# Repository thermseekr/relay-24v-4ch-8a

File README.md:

# RELAY-24V-4CH-8A

Relay board with 4x 24 VDC relays rated for 8A. This board is designed to be used togheter with [ESP-24V-16CH](https://github.com/thermseekr/esp-24v-16ch) and [ESP-24V-32CH](https://github.com/thermseekr/esp-24v-32ch), but can be driven by any 24V control circuit compatible with NPN inputs.

The dimensions are such that the boards can be mounted on a PCB DIN rail holder from the Brazilian manufacturer Metaltex, check [here](https://www.metaltex.com.br/produtos/componentes/suportes/sp7-suporte-para-montagem-de-placa-de-circuito-impresso-em-trilho-din) for details.

Board uses Omron 10A relays and is limited to 8A/channel per copper trace capacity.

## LICENSE

This project is licensed under the [Creative Commons BY-NC 4.0 License](https://creativecommons.org/licenses/by-nc/4.0/).
Commercial use is not permitted without prior written consent. See the [LICENSE.txt](LICENSE.txt) file for details.

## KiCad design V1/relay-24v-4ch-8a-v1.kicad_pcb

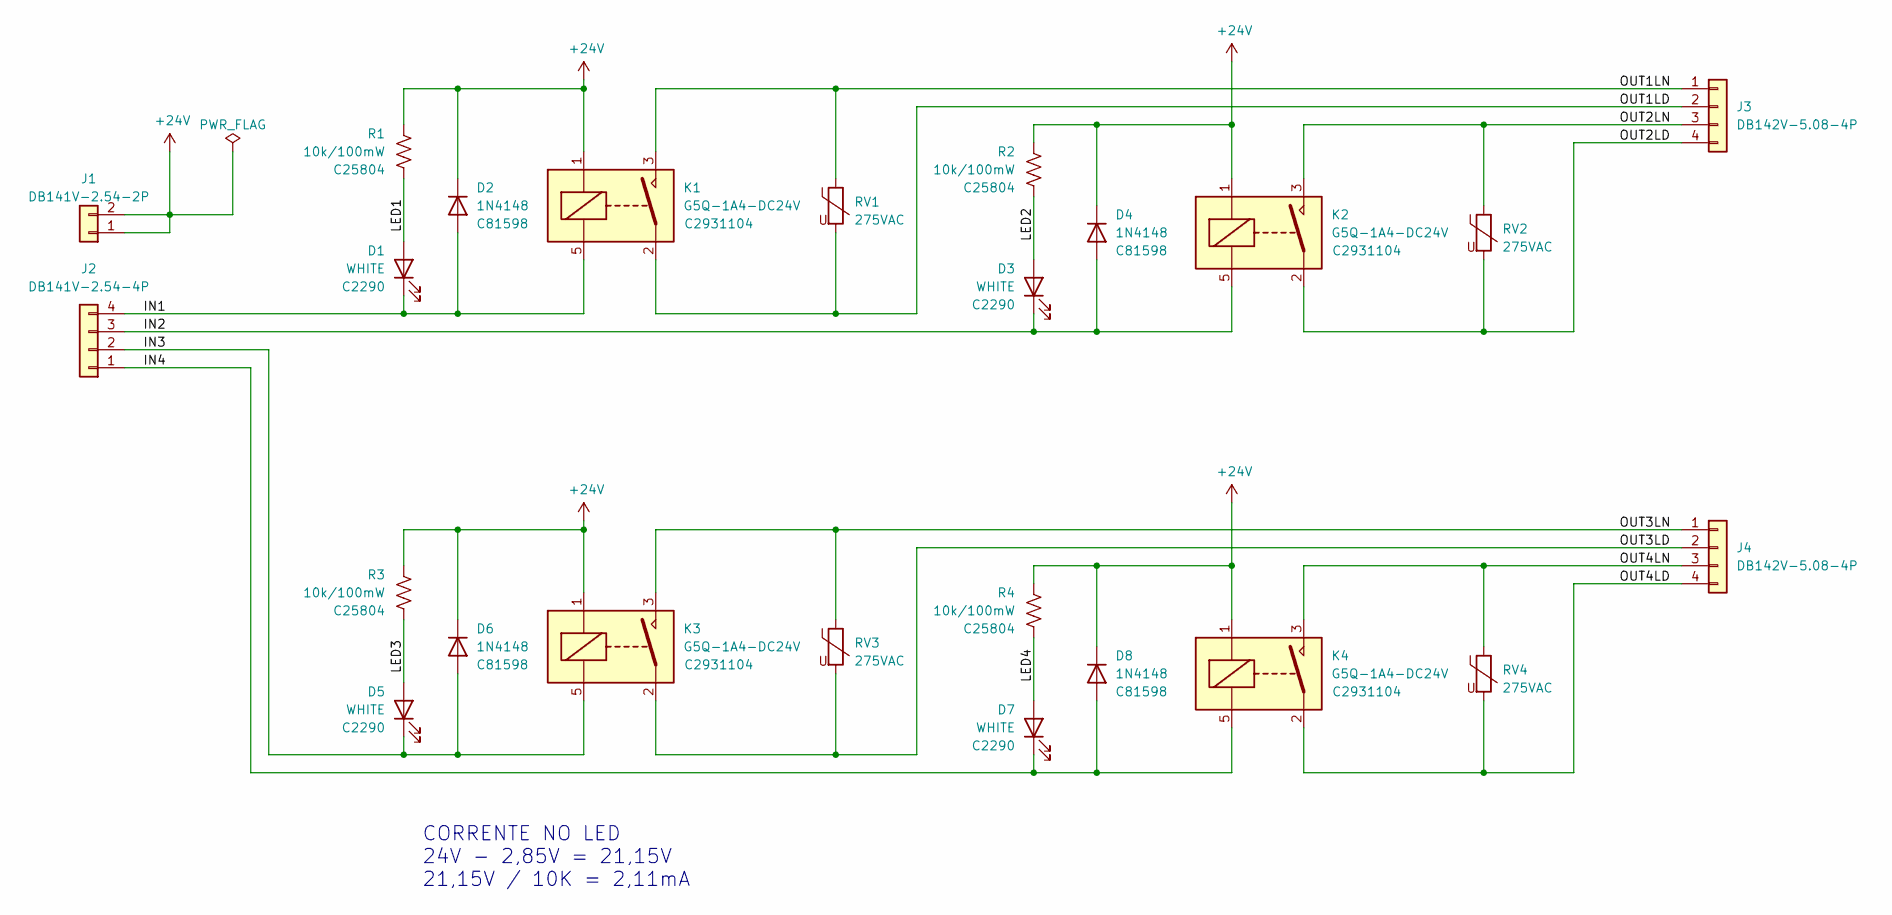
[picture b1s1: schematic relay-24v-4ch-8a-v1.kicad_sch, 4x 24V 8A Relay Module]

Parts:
D1, D3, D5, D7: WHITE; LED_0603_1608Metric; Mfr PN KT-0603W; LCSC Part # C2290
D2, D4, D6, D8: 1N4148; D_SOD-123; Mfr PN 1N4148W; LCSC Part # C81598
J1: DB141V-2.54-2P; TerminalBlock_Dibo_DB141V-2.54-2P_1x02_P2.54mm_Vertical; Mfr PN DB141V-2.54-2P-GN; JLCPCB BOM 1
J2: DB141V-2.54-4P; TerminalBlock_Dibo_DB141V-2.54-4P_1x04_P2.54mm_Vertical; Mfr PN DB141V-2.54-4P-GN; JLCPCB BOM 1
J3, J4: DB142V-5.08-4P; TerminalBlock_Dibo_DB142V-5.08-4P_1x04_P5.08mm_Vertical; Mfr PN DB142V-5.08-4P-GN; JLCPCB BOM 1
K1, K2, K3, K4: G5Q-1A4-DC24V; Relay_SPST_Omron-G5Q-1A; Mfr PN G5Q-1A4-DC24V; JLCPCB BOM 1
R1, R2, R3, R4: 10k/100mW; R_0603_1608Metric; Mfr PN 0603WAF1002T5E; LCSC Part # C25804
RV1, RV2, RV3, RV4: 275VAC; RV_Disc_D9.50mm_W3.6mm_P5.08mm; Mfr PN RM07D431KC1IE100; JLCPCB BOM 1

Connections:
+24V: D2.1 (K), D4.1 (K), D6.1 (K), D8.1 (K), J1.1, J1.2, K1.1, K2.1, K3.1, K4.1, R1.1, R2.1, R3.1, R4.1
/IN1: D1.1 (K), D2.2 (A), J2.4, K1.5
/IN2: D3.1 (K), D4.2 (A), J2.3, K2.5
/IN3: D5.1 (K), D6.2 (A), J2.2, K3.5
/IN4: D7.1 (K), D8.2 (A), J2.1, K4.5
/LED1: D1.2 (A), R1.2
/LED2: D3.2 (A), R2.2
/LED3: D5.2 (A), R3.2
/LED4: D7.2 (A), R4.2
/OUT1LD: J3.2, K1.2, RV1.2
/OUT1LN: J3.1, K1.3, RV1.1
/OUT2LD: J3.4, K2.2, RV2.2
/OUT2LN: J3.3, K2.3, RV2.1
/OUT3LD: J4.2, K3.2, RV3.2
/OUT3LN: J4.1, K3.3, RV3.1
/OUT4LD: J4.4, K4.2, RV4.2
/OUT4LN: J4.3, K4.3, RV4.1

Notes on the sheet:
CORRENTE NO LED 24V - 2,85V = 21,15V 21,15V / 10K = 2,11mA

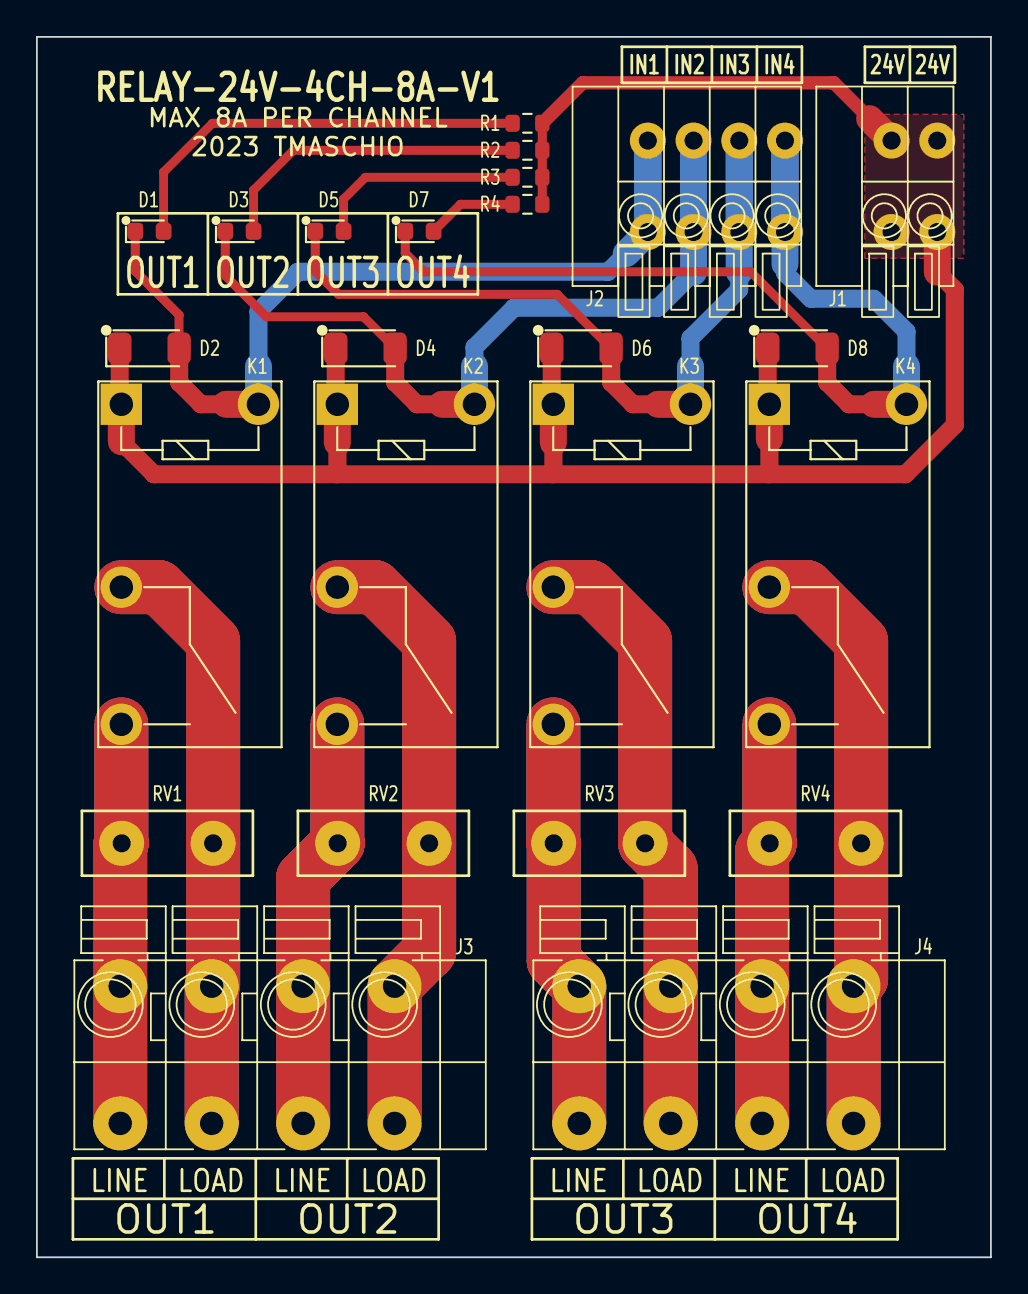
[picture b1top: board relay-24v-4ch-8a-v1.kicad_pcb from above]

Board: 2 copper layers, 53.0 x 67.8 mm, 24 parts (0 on the bottom side), 17 nets.

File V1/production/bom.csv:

Designator,Footprint,Quantity,Value,LCSC Part #
"D1, D3, D5, D7",0603,4,WHITE,C2290
"D2, D4, D6, D8",D_SOD-123,4,1N4148,C81598
J1,TerminalBlock_Dibo_DB141V-2.54-2P_1x02_P2.54mm_Vertical,1,DB141V-2.54-2P,C2898744
J2,TerminalBlock_Dibo_DB141V-2.54-4P_1x04_P2.54mm_Vertical,1,DB141V-2.54-4P,C2898746
"J3, J4",TerminalBlock_Dibo_DB142V-5.08-4P_1x04_P5.08mm_Vertical,2,DB142V-5.08-4P,C2898701
"K1, K2, K3, K4",Relay_SPST_Omron-G5Q-1A,4,G5Q-1A4-DC24V,C2931104
"R1, R2, R3, R4",0603,4,10k/100mW,C25804
"RV1, RV2, RV3, RV4",RV_Disc_D9.50mm_W3.6mm_P5.08mm,4,275VAC,C2761646

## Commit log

2024-11-23 Image updated
2024-11-23 Lock files
2024-11-23 Created production files
2024-11-23 modified: .gitignore new file: V1/production/4x_24V_8A_Relay_Module_V1.zip new file: V1/production/bom.csv new file: V1/production/designators.csv new file: V1/production/positions.csv new file: rela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
2024-11-23 Relay footprint adjusted
2025-04-14 Prefab checks
2025-04-16 Updated footprints
2025-06-22 Updated connectors
2025-06-30 Added license
2025-12-11 Revision before manufacturing
2025-12-11 Revising for fabrication
2025-12-13 Review before fabrication
2025-12-19 Revising before manufacturing.
